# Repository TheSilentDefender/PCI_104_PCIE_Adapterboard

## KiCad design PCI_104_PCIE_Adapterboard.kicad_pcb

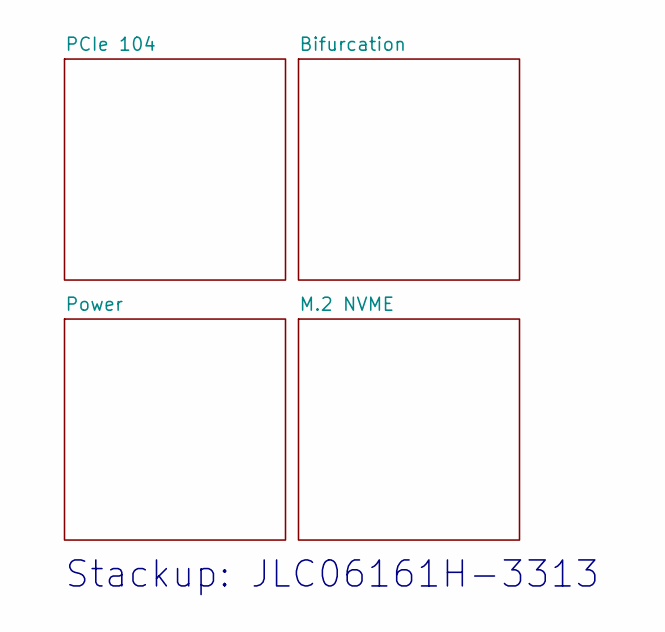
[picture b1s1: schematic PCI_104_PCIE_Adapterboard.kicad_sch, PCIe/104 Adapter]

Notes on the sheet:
Stackup: JLC06161H-3313

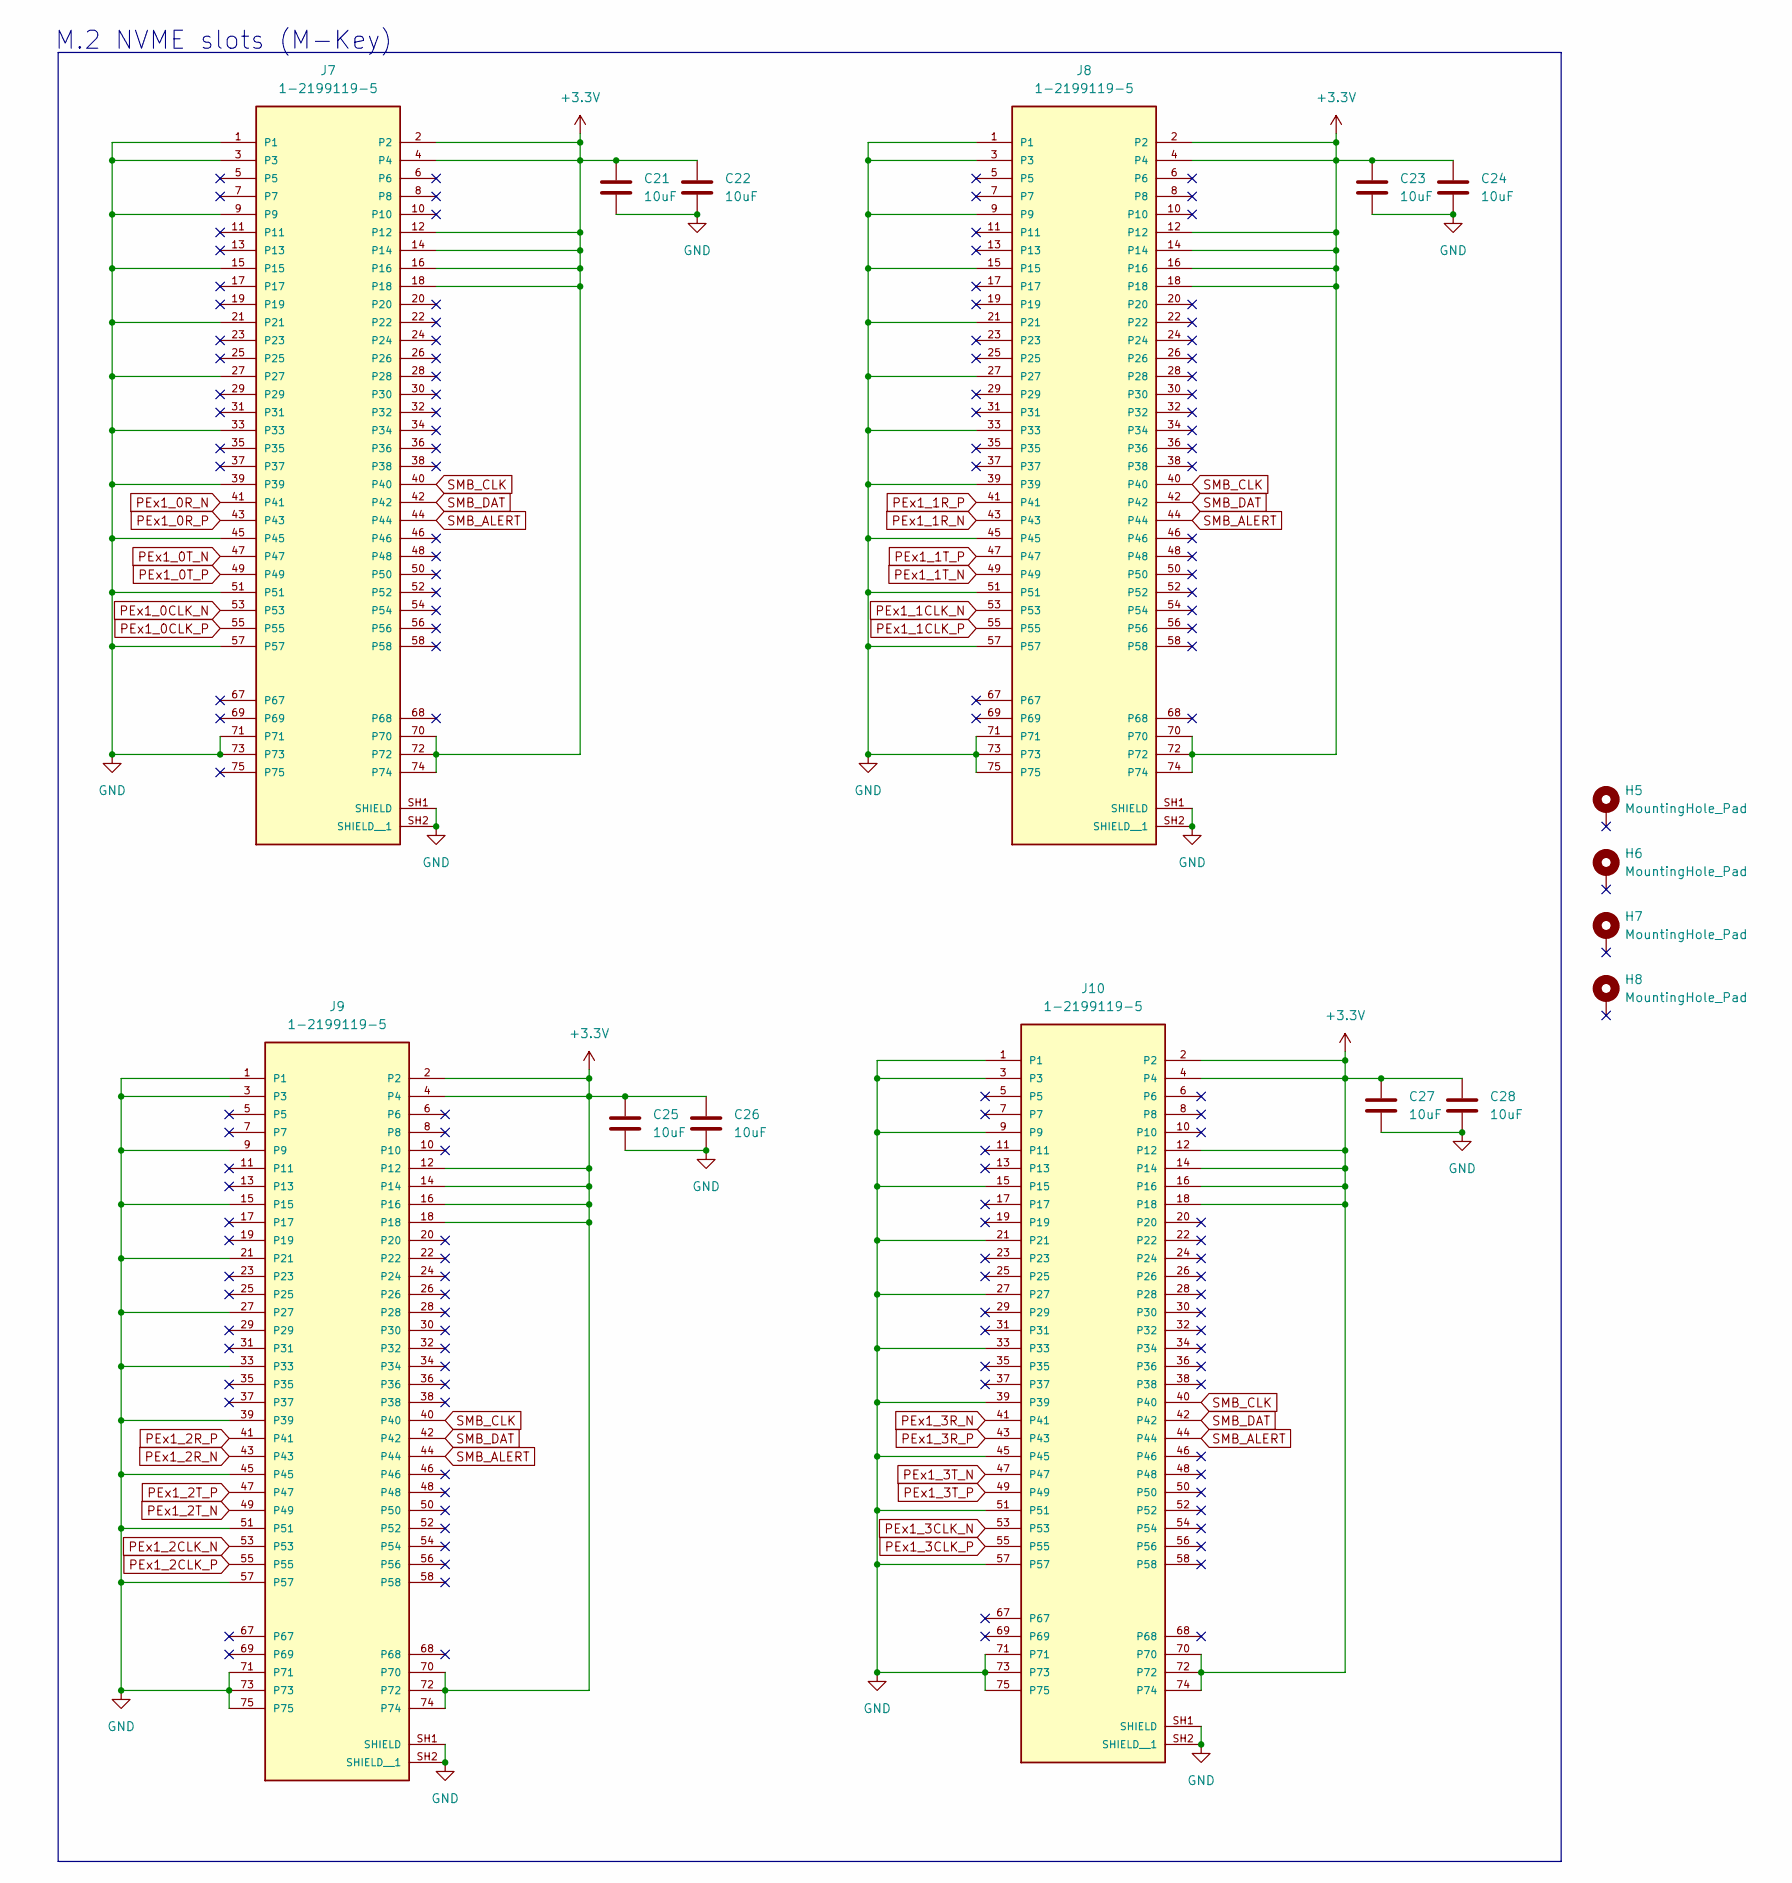
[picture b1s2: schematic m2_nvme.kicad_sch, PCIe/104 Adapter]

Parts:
C21, C22, C23, C24, C25, C26, C27, C28: 10uF; C_0805_2012Metric_Pad1.18x1.45mm_HandSolder
H5, H6, H7, H8: MountingHole_Pad; MountingHole_3.2mm_M3_Pad_TopBottom
J7, J8, J9, J10: 1-2199119-5; TE_1-2199119-5

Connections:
+3.3V: C21.1, C22.1, C23.1, C24.1, C25.1, C26.1, C27.1, C28.1, J7.2, J7.4, J7.12, J7.14, J7.16, J7.18, J7.70, J7.72, J7.74, J8.2, J8.4, J8.12, J8.14, J8.16, J8.18, J8.70, J8.72, J8.74, J9.2, J9.4, J9.12, J9.14, J9.16, J9.18, J9.70, J9.72, J9.74, J10.2, J10.4, J10.12, J10.14, J10.16, J10.18, J10.70, J10.72, J10.74; also elsewhere on the board
GND: C21.2, C22.2, C23.2, C24.2, C25.2, C26.2, C27.2, C28.2, J7.1, J7.3, J7.9, J7.15, J7.21, J7.27, J7.33, J7.39, J7.45, J7.51, J7.57, J7.71, J7.73, J7.SH1 (SHIELD), J7.SH2 (SHIELD__1), J8.1, J8.3, J8.9, J8.15, J8.21, J8.27, J8.33, J8.39, J8.45, J8.51, J8.57, J8.71, J8.73, J8.75, J8.SH1 (SHIELD), J8.SH2 (SHIELD__1), J9.1, J9.3, J9.9, J9.15, J9.21, J9.27, J9.33, J9.39, J9.45, J9.51, J9.57, J9.71, J9.73, J9.75, J9.SH1 (SHIELD), J9.SH2 (SHIELD__1), J10.1, J10.3, J10.9, J10.15, J10.21, J10.27, J10.33, J10.39, J10.45, J10.51, J10.57, J10.71, J10.73, J10.75, J10.SH1 (SHIELD), J10.SH2 (SHIELD__1); also elsewhere on the board
PEx1_0CLK_N: J7.53; also elsewhere on the board
PEx1_0CLK_P: J7.55; also elsewhere on the board
PEx1_0R_N: J7.41; also elsewhere on the board
PEx1_0R_P: J7.43; also elsewhere on the board
PEx1_0T_N: J7.47; also elsewhere on the board
PEx1_0T_P: J7.49; also elsewhere on the board
PEx1_1CLK_N: J8.53; also elsewhere on the board
PEx1_1CLK_P: J8.55; also elsewhere on the board
PEx1_1R_N: J8.43; also elsewhere on the board
PEx1_1R_P: J8.41; also elsewhere on the board
PEx1_1T_N: J8.49; also elsewhere on the board
PEx1_1T_P: J8.47; also elsewhere on the board
PEx1_2CLK_N: J9.53; also elsewhere on the board
PEx1_2CLK_P: J9.55; also elsewhere on the board
PEx1_2R_N: J9.43; also elsewhere on the board
PEx1_2R_P: J9.41; also elsewhere on the board
PEx1_2T_N: J9.49; also elsewhere on the board
PEx1_2T_P: J9.47; also elsewhere on the board
PEx1_3CLK_N: J10.53; also elsewhere on the board
PEx1_3CLK_P: J10.55; also elsewhere on the board
PEx1_3R_N: J10.41; also elsewhere on the board
PEx1_3R_P: J10.43; also elsewhere on the board
PEx1_3T_N: J10.47; also elsewhere on the board
PEx1_3T_P: J10.49; also elsewhere on the board
SMB_ALERT: J7.44, J8.44, J9.44, J10.44; also elsewhere on the board
SMB_CLK: J7.40, J8.40, J9.40, J10.40; also elsewhere on the board
SMB_DAT: J7.42, J8.42, J9.42, J10.42; also elsewhere on the board

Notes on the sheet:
M.2 NVME slots (M-Key)

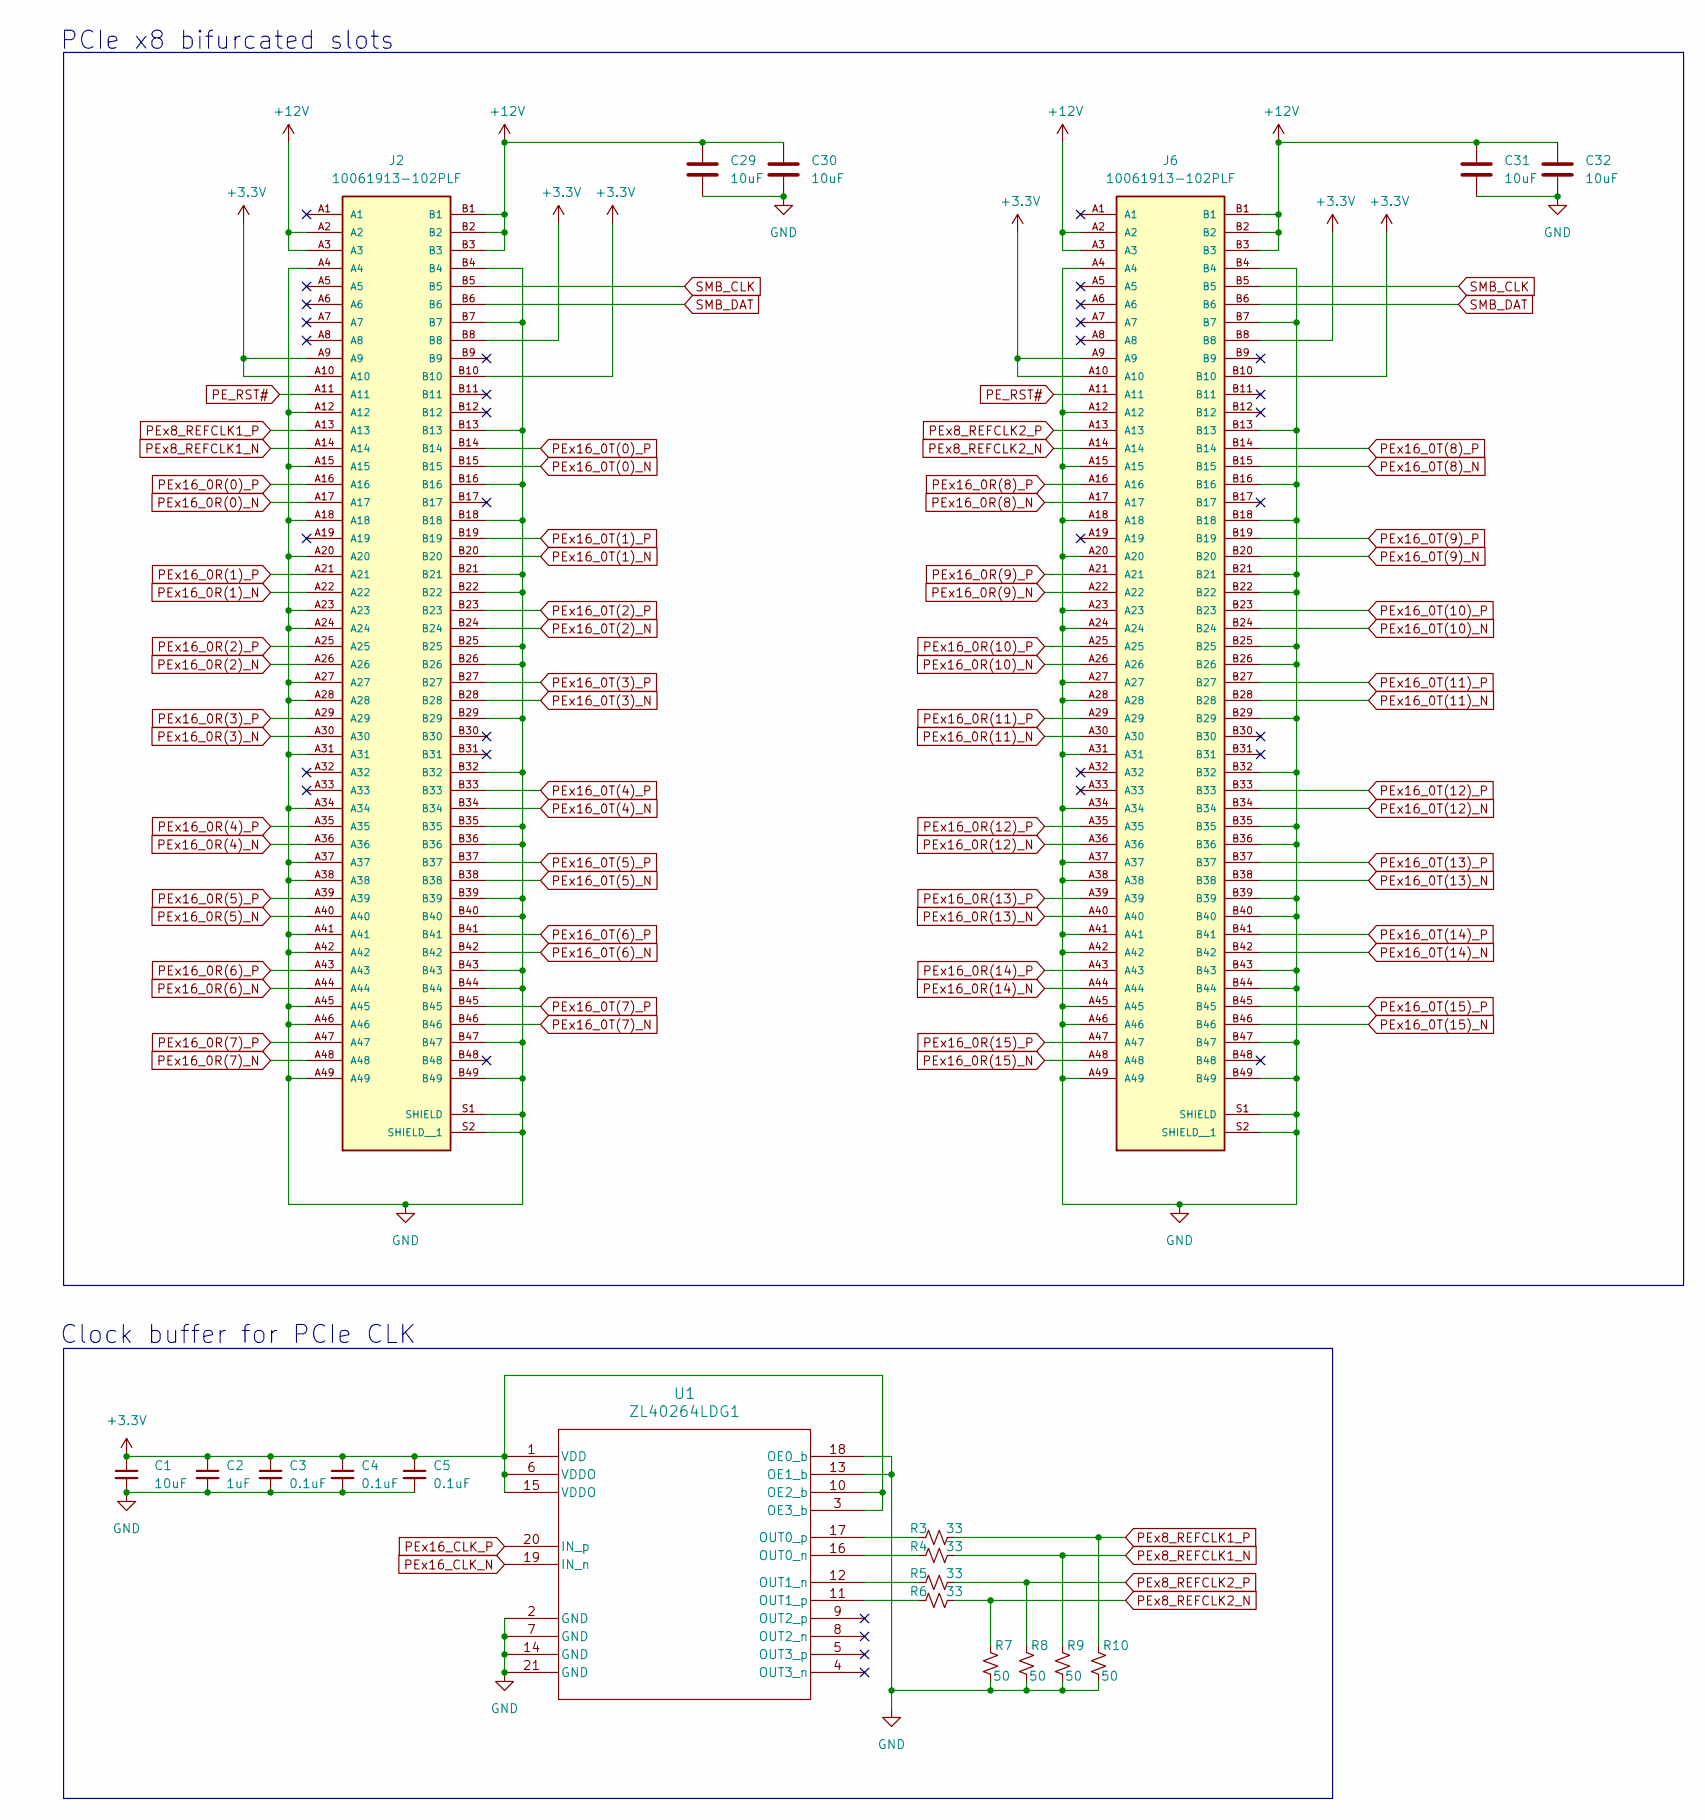
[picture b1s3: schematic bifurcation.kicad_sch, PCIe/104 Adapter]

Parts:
C1, C30: 10uF; C_0805_2012Metric_Pad1.18x1.45mm_HandSolder
C2: 1uF; C_0402_1005Metric
C3, C4, C5: 0.1uF; C_0402_1005Metric
C29, C31, C32: 10uF; C_1206_3216Metric
J2, J6: 10061913-102PLF; AMPHENOL_10061913-102PLF; PARTREV S
R3, R4, R5, R6: 33; R_0402_1005Metric
R7, R8, R9, R10: 50; R_0402_1005Metric
U1: ZL40264LDG1; QFN_264LDG1_MCH

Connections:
+3.3V: C1.1, C2.1, C3.1, C4.1, C5.1, J2.A9, J2.A10, J2.B8, J2.B10, J6.A9, J6.A10, J6.B8, J6.B10, U1.1 (VDD), U1.3 (OE3_b), U1.6 (VDDO), U1.10 (OE2_b), U1.15 (VDDO); also elsewhere on the board
+12V: C29.1, C30.1, C31.1, C32.1, J2.A2, J2.A3, J2.B1, J2.B2, J2.B3, J6.A2, J6.A3, J6.B1, J6.B2, J6.B3; also elsewhere on the board
GND: C1.2, C2.2, C3.2, C4.2, C5.2, C29.2, C30.2, C31.2, C32.2, J2.A4, J2.A12, J2.A15, J2.A18, J2.A20, J2.A23, J2.A24, J2.A27, J2.A28, J2.A31, J2.A34, J2.A37, J2.A38, J2.A41, J2.A42, J2.A45, J2.A46, J2.A49, J2.B4, J2.B7, J2.B13, J2.B16, J2.B18, J2.B21, J2.B22, J2.B25, J2.B26, J2.B29, J2.B32, J2.B35, J2.B36, J2.B39, J2.B40, J2.B43, J2.B44, J2.B47, J2.B49, J2.S1 (SHIELD), J2.S2 (SHIELD__1), J6.A4, J6.A12, J6.A15, J6.A18, J6.A20, J6.A23, J6.A24, J6.A27, J6.A28, J6.A31, J6.A34, J6.A37, J6.A38, J6.A41, J6.A42, J6.A45, J6.A46, J6.A49, J6.B4, J6.B7, J6.B13, J6.B16, J6.B18, J6.B21, J6.B22, J6.B25, J6.B26, J6.B29, J6.B32, J6.B35, J6.B36, J6.B39, J6.B40, J6.B43, J6.B44, J6.B47, J6.B49, J6.S1 (SHIELD), J6.S2 (SHIELD__1), R7.2, R8.2, R9.2, R10.2, U1.2 (GND), U1.7 (GND), U1.13 (OE1_b), U1.14 (GND), U1.18 (OE0_b), U1.21 (GND); also elsewhere on the board
unnamed: R4.1, U1.16 (OUT0_n)
unnamed: R3.1, U1.17 (OUT0_p)
unnamed: R5.1, U1.12 (OUT1_n)
unnamed: R6.1, U1.11 (OUT1_p)
PE_RST#: J2.A11, J6.A11; also elsewhere on the board
PEx8_REFCLK1_N: J2.A14, R4.2, R9.1
PEx8_REFCLK1_P: J2.A13, R3.2, R10.1
PEx8_REFCLK2_N: J6.A14, R6.2, R7.1
PEx8_REFCLK2_P: J6.A13, R5.2, R8.1
PEx16_0R(0)_N: J2.A17; also elsewhere on the board
PEx16_0R(0)_P: J2.A16; also elsewhere on the board
PEx16_0R(1)_N: J2.A22; also elsewhere on the board
PEx16_0R(1)_P: J2.A21; also elsewhere on the board
PEx16_0R(2)_N: J2.A26; also elsewhere on the board
PEx16_0R(2)_P: J2.A25; also elsewhere on the board
PEx16_0R(3)_N: J2.A30; also elsewhere on the board
PEx16_0R(3)_P: J2.A29; also elsewhere on the board
PEx16_0R(4)_N: J2.A36; also elsewhere on the board
PEx16_0R(4)_P: J2.A35; also elsewhere on the board
PEx16_0R(5)_N: J2.A40; also elsewhere on the board
PEx16_0R(5)_P: J2.A39; also elsewhere on the board
PEx16_0R(6)_N: J2.A44; also elsewhere on the board
PEx16_0R(6)_P: J2.A43; also elsewhere on the board
PEx16_0R(7)_N: J2.A48; also elsewhere on the board
PEx16_0R(7)_P: J2.A47; also elsewhere on the board
PEx16_0R(8)_N: J6.A17; also elsewhere on the board
PEx16_0R(8)_P: J6.A16; also elsewhere on the board
PEx16_0R(9)_N: J6.A22; also elsewhere on the board
PEx16_0R(9)_P: J6.A21; also elsewhere on the board
PEx16_0R(10)_N: J6.A26; also elsewhere on the board
PEx16_0R(10)_P: J6.A25; also elsewhere on the board
PEx16_0R(11)_N: J6.A30; also elsewhere on the board
PEx16_0R(11)_P: J6.A29; also elsewhere on the board
PEx16_0R(12)_N: J6.A36; also elsewhere on the board
PEx16_0R(12)_P: J6.A35; also elsewhere on the board
PEx16_0R(13)_N: J6.A40; also elsewhere on the board
PEx16_0R(13)_P: J6.A39; also elsewhere on the board
PEx16_0R(14)_N: J6.A44; also elsewhere on the board
PEx16_0R(14)_P: J6.A43; also elsewhere on the board
PEx16_0R(15)_N: J6.A48; also elsewhere on the board
PEx16_0R(15)_P: J6.A47; also elsewhere on the board
PEx16_0T(0)_N: J2.B15; also elsewhere on the board
PEx16_0T(0)_P: J2.B14; also elsewhere on the board
PEx16_0T(1)_N: J2.B20; also elsewhere on the board
PEx16_0T(1)_P: J2.B19; also elsewhere on the board
PEx16_0T(2)_N: J2.B24; also elsewhere on the board
PEx16_0T(2)_P: J2.B23; also elsewhere on the board
PEx16_0T(3)_N: J2.B28; also elsewhere on the board
PEx16_0T(3)_P: J2.B27; also elsewhere on the board
PEx16_0T(4)_N: J2.B34; also elsewhere on the board
PEx16_0T(4)_P: J2.B33; also elsewhere on the board
PEx16_0T(5)_N: J2.B38; also elsewhere on the board
PEx16_0T(5)_P: J2.B37; also elsewhere on the board
PEx16_0T(6)_N: J2.B42; also elsewhere on the board
PEx16_0T(6)_P: J2.B41; also elsewhere on the board
PEx16_0T(7)_N: J2.B46; also elsewhere on the board
PEx16_0T(7)_P: J2.B45; also elsewhere on the board
PEx16_0T(8)_N: J6.B15; also elsewhere on the board
PEx16_0T(8)_P: J6.B14; also elsewhere on the board
PEx16_0T(9)_N: J6.B20; also elsewhere on the board
PEx16_0T(9)_P: J6.B19; also elsewhere on the board
PEx16_0T(10)_N: J6.B24; also elsewhere on the board
PEx16_0T(10)_P: J6.B23; also elsewhere on the board
PEx16_0T(11)_N: J6.B28; also elsewhere on the board
PEx16_0T(11)_P: J6.B27; also elsewhere on the board
PEx16_0T(12)_N: J6.B34; also elsewhere on the board
PEx16_0T(12)_P: J6.B33; also elsewhere on the board
PEx16_0T(13)_N: J6.B38; also elsewhere on the board
PEx16_0T(13)_P: J6.B37; also elsewhere on the board
PEx16_0T(14)_N: J6.B42; also elsewhere on the board
PEx16_0T(14)_P: J6.B41; also elsewhere on the board
PEx16_0T(15)_N: J6.B46; also elsewhere on the board
PEx16_0T(15)_P: J6.B45; also elsewhere on the board
PEx16_CLK_N: U1.19 (IN_n); also elsewhere on the board
PEx16_CLK_P: U1.20 (IN_p); also elsewhere on the board
SMB_CLK: J2.B5, J6.B5; also elsewhere on the board
SMB_DAT: J2.B6, J6.B6; also elsewhere on the board

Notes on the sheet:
PCIe x8 bifurcated slots
Clock buffer for PCIe CLK

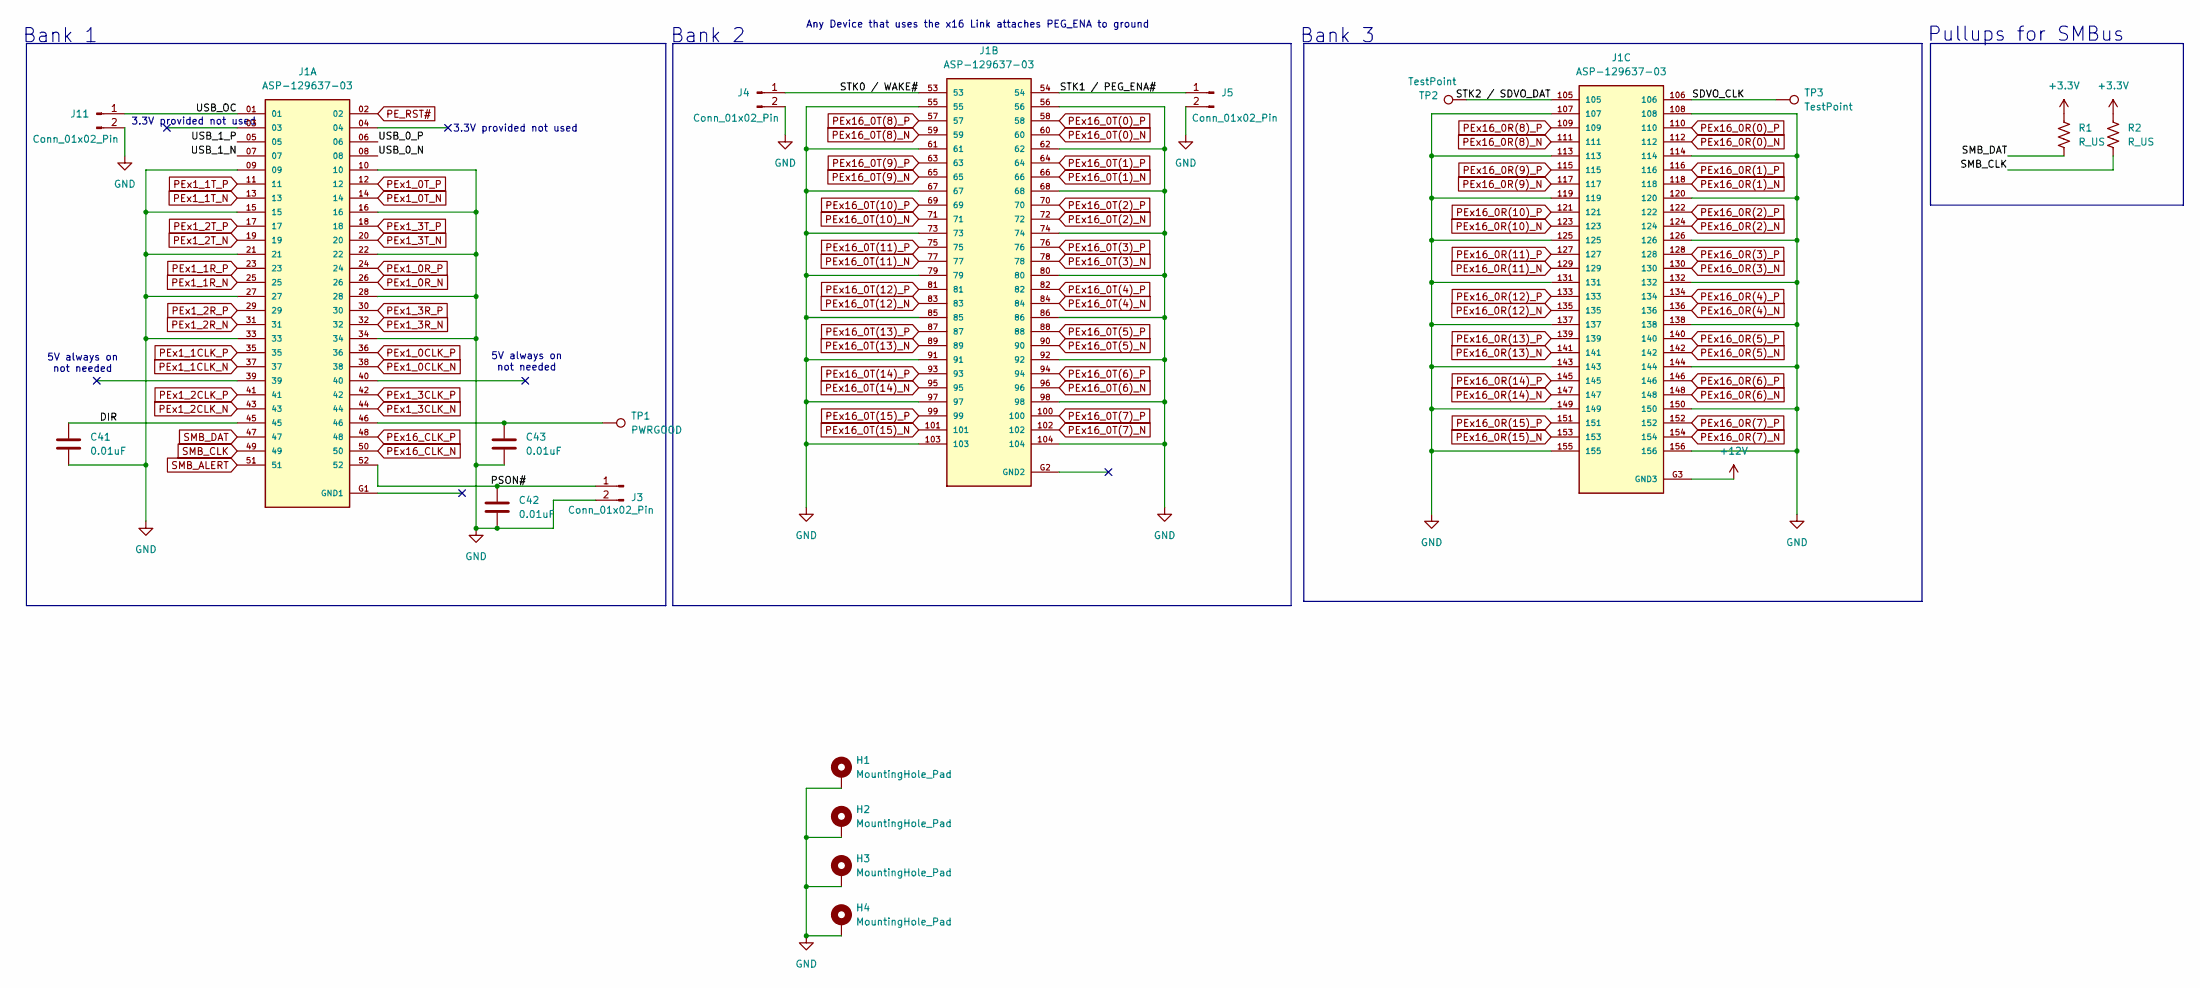
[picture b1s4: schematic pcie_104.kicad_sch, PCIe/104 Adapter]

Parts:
C41, C42, C43: 0.01uF; C_0402_1005Metric
H1, H2, H3, H4: MountingHole_Pad; MountingHole_3.2mm_M3_Pad_TopBottom
J1: ASP-129637-03; SAMTEC_ASP-129637-03; PARTREV D
J3, J4, J5, J11: Conn_01x02_Pin; PinHeader_1x02_P2.54mm_Vertical
R1, R2: R_US; R_0603_1608Metric_Pad0.98x0.95mm_HandSolder
TP1: PWRGOOD; TestPoint_Keystone_5015_Micro_Mini
TP2, TP3: TestPoint; TestPoint_Keystone_5015_Micro_Mini

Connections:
+3.3V: R1.1, R2.1; also elsewhere on the board
+12V: J1.G3 (GND3); also elsewhere on the board
/PCIe 104/DIR: C41.1, J1.45
/PCIe 104/PSON#: C42.1, J1.52, J3.1
/PCIe 104/SDVO_CLK: J1.106, TP3.1
/PCIe 104/STK0 / WAKE#: J1.53, J4.1
/PCIe 104/STK1 / PEG_ENA#: J1.54, J5.1
/PCIe 104/STK2 / SDVO_DAT: J1.105, TP2.1
/PCIe 104/USB_0_N: J1.08
/PCIe 104/USB_0_P: J1.06
/PCIe 104/USB_1_N: J1.07
/PCIe 104/USB_1_P: J1.05
/PCIe 104/USB_OC: J1.01, J11.1
GND: C41.2, C42.2, C43.2, H1.1, H2.1, H3.1, H4.1, J1.09, J1.10, J1.15, J1.16, J1.21, J1.22, J1.27, J1.28, J1.33, J1.34, J1.55, J1.56, J1.61, J1.62, J1.67, J1.68, J1.73, J1.74, J1.79, J1.80, J1.85, J1.86, J1.91, J1.92, J1.97, J1.98, J1.103, J1.104, J1.107, J1.108, J1.113, J1.114, J1.119, J1.120, J1.125, J1.126, J1.131, J1.132, J1.137, J1.138, J1.143, J1.144, J1.149, J1.150, J1.155, J1.156, J3.2, J4.2, J5.2, J11.2; also elsewhere on the board
unnamed: C43.1, J1.46, TP1.1
PE_RST#: J1.02; also elsewhere on the board
PEx1_0CLK_N: J1.38; also elsewhere on the board
PEx1_0CLK_P: J1.36; also elsewhere on the board
PEx1_0R_N: J1.26; also elsewhere on the board
PEx1_0R_P: J1.24; also elsewhere on the board
PEx1_0T_N: J1.14; also elsewhere on the board
PEx1_0T_P: J1.12; also elsewhere on the board
PEx1_1CLK_N: J1.37; also elsewhere on the board
PEx1_1CLK_P: J1.35; also elsewhere on the board
PEx1_1R_N: J1.25; also elsewhere on the board
PEx1_1R_P: J1.23; also elsewhere on the board
PEx1_1T_N: J1.13; also elsewhere on the board
PEx1_1T_P: J1.11; also elsewhere on the board
PEx1_2CLK_N: J1.43; also elsewhere on the board
PEx1_2CLK_P: J1.41; also elsewhere on the board
PEx1_2R_N: J1.31; also elsewhere on the board
PEx1_2R_P: J1.29; also elsewhere on the board
PEx1_2T_N: J1.19; also elsewhere on the board
PEx1_2T_P: J1.17; also elsewhere on the board
PEx1_3CLK_N: J1.44; also elsewhere on the board
PEx1_3CLK_P: J1.42; also elsewhere on the board
PEx1_3R_N: J1.32; also elsewhere on the board
PEx1_3R_P: J1.30; also elsewhere on the board
PEx1_3T_N: J1.20; also elsewhere on the board
PEx1_3T_P: J1.18; also elsewhere on the board
PEx16_0R(0)_N: J1.112; also elsewhere on the board
PEx16_0R(0)_P: J1.110; also elsewhere on the board
PEx16_0R(1)_N: J1.118; also elsewhere on the board
PEx16_0R(1)_P: J1.116; also elsewhere on the board
PEx16_0R(2)_N: J1.124; also elsewhere on the board
PEx16_0R(2)_P: J1.122; also elsewhere on the board
PEx16_0R(3)_N: J1.130; also elsewhere on the board
PEx16_0R(3)_P: J1.128; also elsewhere on the board
PEx16_0R(4)_N: J1.136; also elsewhere on the board
PEx16_0R(4)_P: J1.134; also elsewhere on the board
PEx16_0R(5)_N: J1.142; also elsewhere on the board
PEx16_0R(5)_P: J1.140; also elsewhere on the board
PEx16_0R(6)_N: J1.148; also elsewhere on the board
PEx16_0R(6)_P: J1.146; also elsewhere on the board
PEx16_0R(7)_N: J1.154; also elsewhere on the board
PEx16_0R(7)_P: J1.152; also elsewhere on the board
PEx16_0R(8)_N: J1.111; also elsewhere on the board
PEx16_0R(8)_P: J1.109; also elsewhere on the board
PEx16_0R(9)_N: J1.117; also elsewhere on the board
PEx16_0R(9)_P: J1.115; also elsewhere on the board
PEx16_0R(10)_N: J1.123; also elsewhere on the board
PEx16_0R(10)_P: J1.121; also elsewhere on the board
PEx16_0R(11)_N: J1.129; also elsewhere on the board
PEx16_0R(11)_P: J1.127; also elsewhere on the board
PEx16_0R(12)_N: J1.135; also elsewhere on the board
PEx16_0R(12)_P: J1.133; also elsewhere on the board
PEx16_0R(13)_N: J1.141; also elsewhere on the board
PEx16_0R(13)_P: J1.139; also elsewhere on the board
PEx16_0R(14)_N: J1.147; also elsewhere on the board
PEx16_0R(14)_P: J1.145; also elsewhere on the board
PEx16_0R(15)_N: J1.153; also elsewhere on the board
PEx16_0R(15)_P: J1.151; also elsewhere on the board
PEx16_0T(0)_N: J1.60; also elsewhere on the board
PEx16_0T(0)_P: J1.58; also elsewhere on the board
PEx16_0T(1)_N: J1.66; also elsewhere on the board
PEx16_0T(1)_P: J1.64; also elsewhere on the board
PEx16_0T(2)_N: J1.72; also elsewhere on the board
PEx16_0T(2)_P: J1.70; also elsewhere on the board
PEx16_0T(3)_N: J1.78; also elsewhere on the board
PEx16_0T(3)_P: J1.76; also elsewhere on the board
PEx16_0T(4)_N: J1.84; also elsewhere on the board
PEx16_0T(4)_P: J1.82; also elsewhere on the board
PEx16_0T(5)_N: J1.90; also elsewhere on the board
PEx16_0T(5)_P: J1.88; also elsewhere on the board
PEx16_0T(6)_N: J1.96; also elsewhere on the board
PEx16_0T(6)_P: J1.94; also elsewhere on the board
PEx16_0T(7)_N: J1.102; also elsewhere on the board
PEx16_0T(7)_P: J1.100; also elsewhere on the board
PEx16_0T(8)_N: J1.59; also elsewhere on the board
PEx16_0T(8)_P: J1.57; also elsewhere on the board
PEx16_0T(9)_N: J1.65; also elsewhere on the board
PEx16_0T(9)_P: J1.63; also elsewhere on the board
PEx16_0T(10)_N: J1.71; also elsewhere on the board
PEx16_0T(10)_P: J1.69; also elsewhere on the board
PEx16_0T(11)_N: J1.77; also elsewhere on the board
PEx16_0T(11)_P: J1.75; also elsewhere on the board
PEx16_0T(12)_N: J1.83; also elsewhere on the board
PEx16_0T(12)_P: J1.81; also elsewhere on the board
PEx16_0T(13)_N: J1.89; also elsewhere on the board
PEx16_0T(13)_P: J1.87; also elsewhere on the board
PEx16_0T(14)_N: J1.95; also elsewhere on the board
PEx16_0T(14)_P: J1.93; also elsewhere on the board
PEx16_0T(15)_N: J1.101; also elsewhere on the board
PEx16_0T(15)_P: J1.99; also elsewhere on the board
PEx16_CLK_N: J1.50; also elsewhere on the board
PEx16_CLK_P: J1.48; also elsewhere on the board
SMB_ALERT: J1.51; also elsewhere on the board
SMB_CLK: J1.49, R2.2; also elsewhere on the board
SMB_DAT: J1.47, R1.2; also elsewhere on the board

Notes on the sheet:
Bank 2
Pullups for SMBus
3.3V provided not used
Any Device that uses the x16 Link attaches PEG_ENA to ground
5V always on not needed
Bank 3
Bank 1

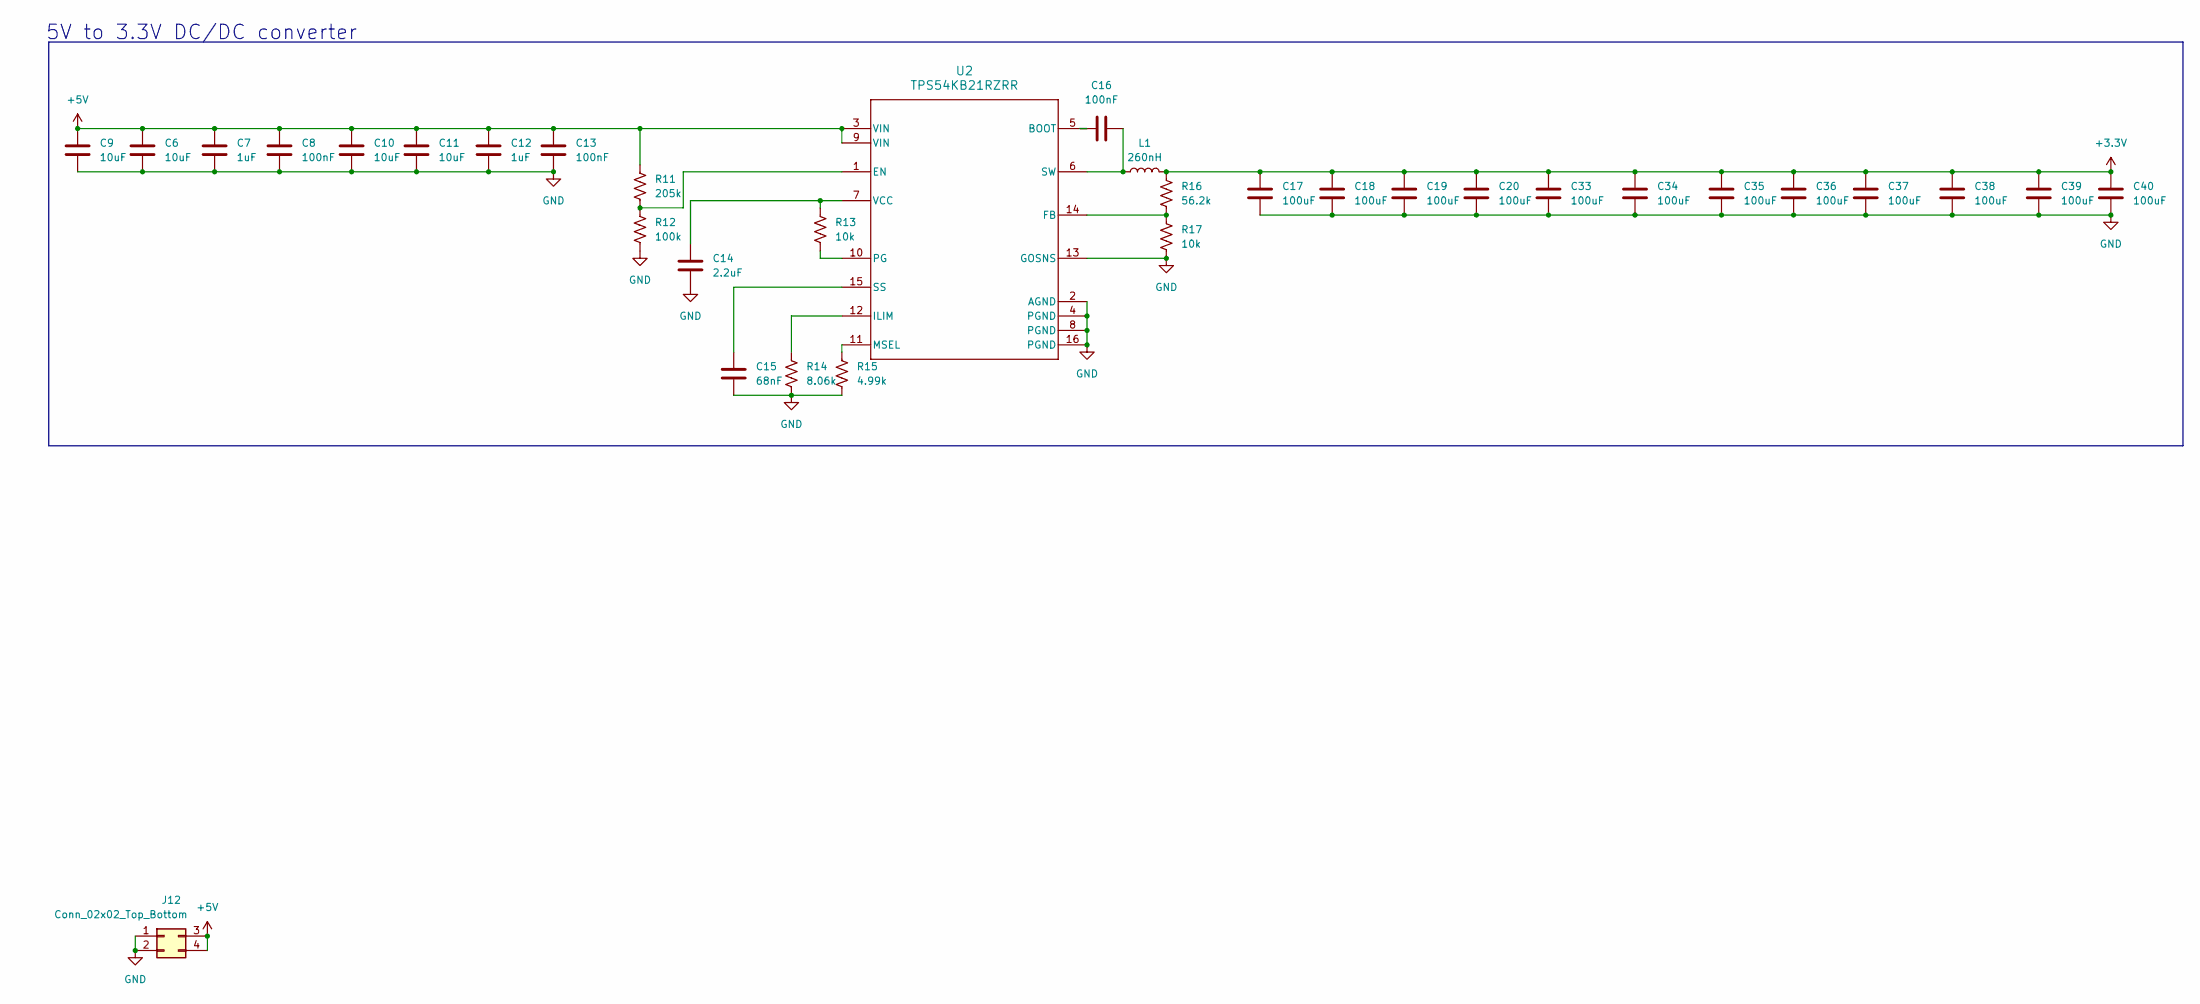
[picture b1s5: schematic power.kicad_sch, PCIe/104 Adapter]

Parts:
C6, C9, C10, C11: 10uF; C_0805_2012Metric_Pad1.18x1.45mm_HandSolder
C7, C12: 1uF; C_0402_1005Metric
C8, C13, C16: 100nF; C_0402_1005Metric
C14: 2.2uF; C_0402_1005Metric
C15: 68nF; C_0402_1005Metric
C17, C18, C19, C20, C33, C34, C35, C36, C37, C38, C39, C40: 100uF; C_1206_3216Metric
J12: Conn_02x02_Top_Bottom; Molex_Mini-Fit_Jr_5569-04A1_2x02_P4.20mm_Horizontal
L1: 260nH; L_Coilcraft_XAL1010-XXX
R11: 205k; R_0402_1005Metric
R12: 100k; R_0402_1005Metric
R13, R17: 10k; R_0402_1005Metric
R14: 8.06k; R_0402_1005Metric
R15: 4.99k; R_0402_1005Metric
R16: 56.2k; R_0402_1005Metric
U2: TPS54KB21RZRR; RZR0016A-MFG

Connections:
+3.3V: C17.1, C18.1, C19.1, C20.1, C33.1, C34.1, C35.1, C36.1, C37.1, C38.1, C39.1, C40.1, L1.2, R16.2; also elsewhere on the board
+5V: C6.1, C7.1, C8.1, C9.1, C10.1, C11.1, C12.1, C13.1, J12.3, J12.4, R11.1, U2.3 (VIN), U2.9 (VIN)
GND: C6.2, C7.2, C8.2, C9.2, C10.2, C11.2, C12.2, C13.2, C14.2, C15.2, C17.2, C18.2, C19.2, C20.2, C33.2, C34.2, C35.2, C36.2, C37.2, C38.2, C39.2, C40.2, J12.1, J12.2, R12.2, R14.1, R15.1, R17.1, U2.2 (AGND), U2.4 (PGND), U2.8 (PGND), U2.13 (GOSNS), U2.16 (PGND); also elsewhere on the board
unnamed: C16.1, U2.5 (BOOT)
unnamed: R11.2, R12.1, U2.1 (EN)
unnamed: R16.1, R17.2, U2.14 (FB)
unnamed: R14.2, U2.12 (ILIM)
unnamed: R15.2, U2.11 (MSEL)
unnamed: R13.1, U2.10 (PG)
unnamed: C15.1, U2.15 (SS)
unnamed: C16.2, L1.1, U2.6 (SW)
unnamed: C14.1, R13.2, U2.7 (VCC)

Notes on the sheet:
5V to 3.3V DC/DC converter

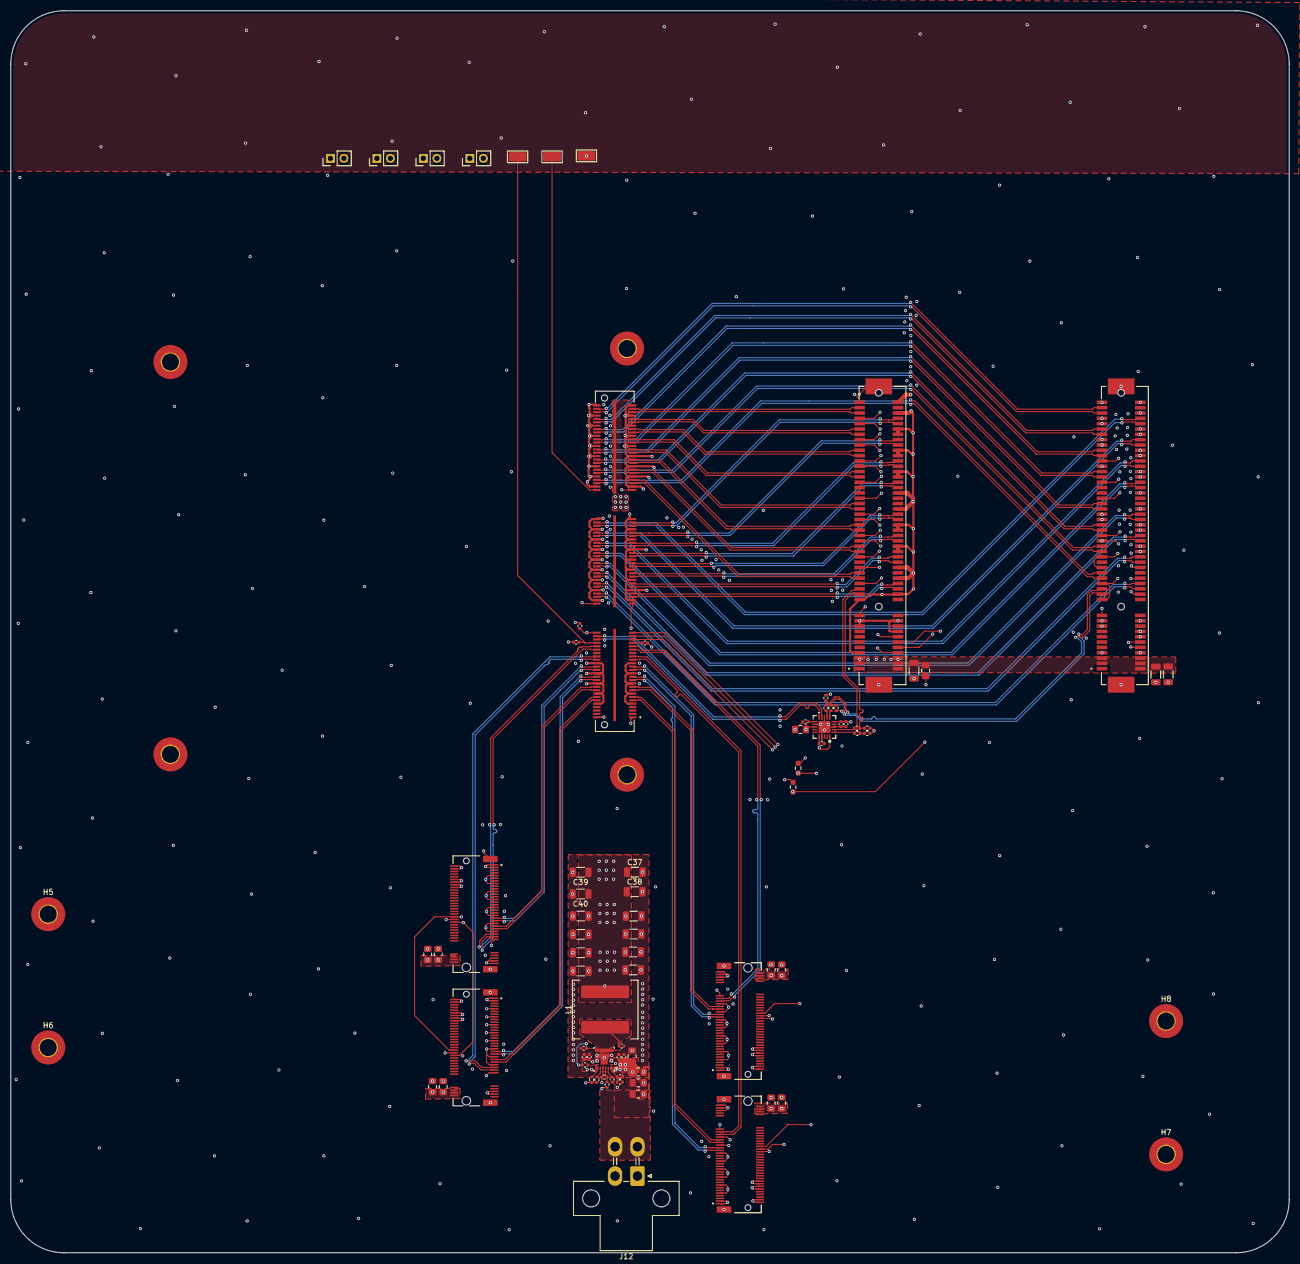
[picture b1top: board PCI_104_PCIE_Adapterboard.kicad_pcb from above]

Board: 6 copper layers, 240.0 x 233.2 mm, 86 parts (0 on the bottom side), 123 nets.

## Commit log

2025-06-11 schem mostly complete
2025-06-16 finished schem
2025-06-24 pcie traces routed
2025-06-24 changed trave width
2025-06-26 layout done!!
2025-06-26 layout complete
2025-06-26 schem pdf updated
2025-06-26 stitched gnd planes
